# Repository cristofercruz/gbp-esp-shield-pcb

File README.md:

# Game Boy WiFi Printer - D1 Mini Shield  

<a href="https://oshpark.com/shared_projects/7WqZCkn1"></img></a>

Enthusiasts on the [Game Boy Camera Club discord server](http://bit.ly/gbccd) have been working on a Game Boy Printer emulator project based on ESP8266 D1 mini boards. Taking inspiration from other projects like the [Gameboy Link Cable Breakout PCB](https://github.com/Palmr/gb-link-cable), I created this shield board to add a link connector and pinouts for an oled screen.

Here's a render of the PCB  

# Recommended D1 mini Boards:  
**LILYGO TTGO D1 mini** (recommended) - https://www.aliexpress.com/item/4001144115302.html  
Embedded 16340 battery holder, embedded charge curcuit, and embedded power switch.

**LOLIN D1 mini Pro** - https://www.aliexpress.com/item/32724692514.html  
Embedded LiPo battery connector, embedded charge circuit. No embedded power switch.

**LOLIN D1 mini** - https://www.aliexpress.com/item/32529101036.html  
No battery connector, no charge curcit, and no power switch included.

# Assembled Printer Example  
Here's a photo of an assembled printer using a D1 mini Pro board:  

# Components  
Besides the ESP8266 board, this shield uses the following components:

* 1× 4.7kΩ resistor (*required for link detection*)
* 1x 10kΩ resistor (*required for link detection*)
* 1× 128×32 OLED display (*optional, recommended*)
* 1× 3.5mm LED (*optional*)

Placements for the components are clearly marked on the board's silkscreen. The resistors can be either through hole or surface mount type and can be placed either on the top OR bottom of the board.

# Compatible Software  
This shield breaks out appropriate pins for the Game Boy Link port that is part of the PCB itself. This hardware is suitable for both the [Arduino Game Boy Printer Emulator](https://github.com/mofosyne/arduino-gameboy-printer-emulator) as well as the [WiFi Game Boy Printer Emulator](https://github.com/HerrZatacke/wifi-gbp-emulator)

When using this with the WiFi Game Boy Printer Emulator, you can uncomment and adjust the pin on the following lines in your `config.h` file to detect a connected and powered on Game Boy to auto switch into print mode:  
```
// Sense boot mode lets you use the signal on pin GB_5V_OUT to determine printer/server mode
#define SENSE_BOOT_MODE
#define GB_5V_OUT 16
```

If you've added the optional OLED display, you can uncomment and adjust the pins on the following lines in your `config.h` file:  
```
// Uncomment if using an adafruit oled display
#define USE_OLED
// Alternative OLED Pins
#define OLED_SDA 4
#define OLED_SCL 5
```

# Usage 

When connecting a Game Boy Link cable to the shield, check the silkscreen for indicators on which side should be placed up. (The flat side of the connector should face down and the rounded side should face up, the same side as the OLED screen.)

You can get help with this project and find info on the software that runs on the ESP by joining the [Game Boy Camera Club discord server](http://bit.ly/gbccd)

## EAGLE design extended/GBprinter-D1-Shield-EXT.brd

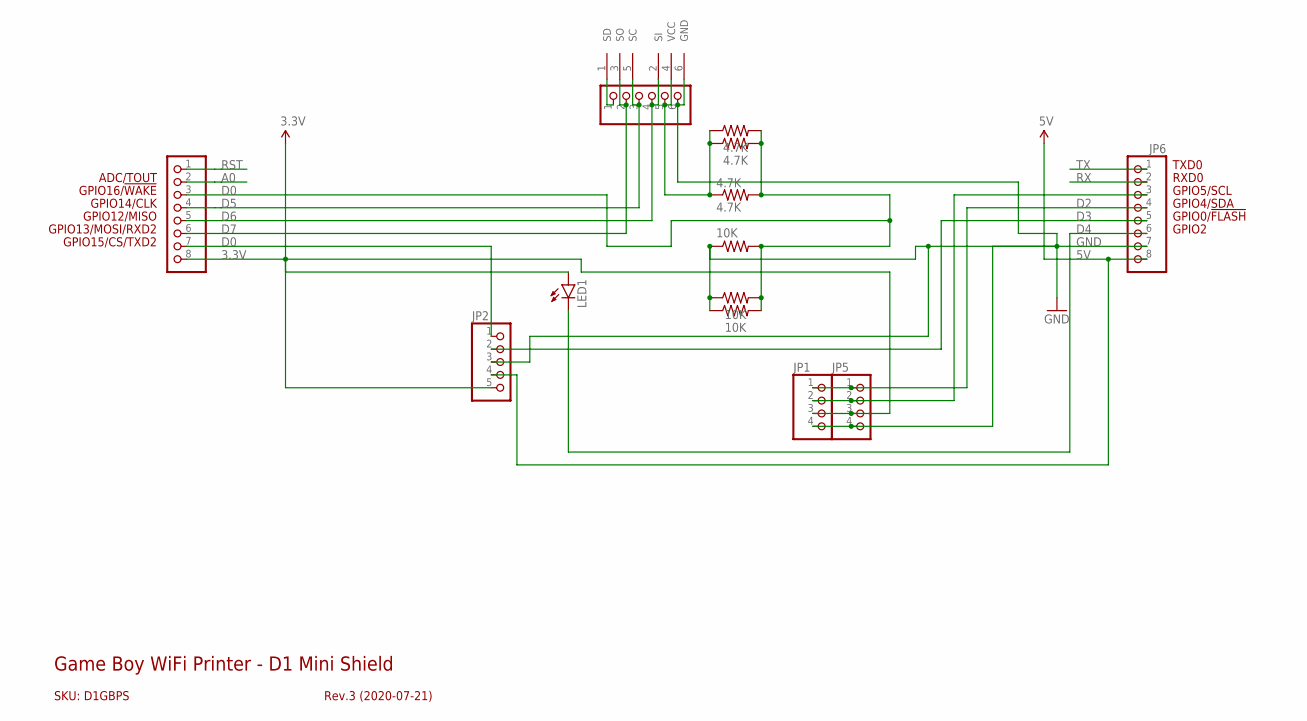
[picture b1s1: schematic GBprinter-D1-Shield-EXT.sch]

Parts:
4.7K: 4.7K; 0207/10
10K: 10K; 0207/10
JP1, JP5: PINHD-1X4/OCT; 1X04/OCT
JP2: PINHD-1X5/OCT; 1X05/OCT
JP3, JP6: PINHD-1X8/OCT; 1X08/OCT
JP4: PINHD-1X6/OCT; 1X06/OCT
LED1: LED3MM
R1, R5: 4.7K; RESC2012X65
R2, R3: 10K; RESC2012X65
U$2: GB-LINK-PADS; GB-LINK-PCB

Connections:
3.3V: JP1.3, JP2.5, JP3.8, JP5.3, LED1.A
5V: JP2.4, JP6.8
A0: JP3.2
D0: 4.7K.2, 10K.2, JP3.3, R1.2, R2.2, R3.2, R5.2
D1: JP1.2, JP5.2, JP6.3
D2: JP1.1, JP5.1, JP6.4
D3: JP2.2, JP6.5
D4: JP6.6, LED1.K (C)
D5: JP3.4, JP4.3, U$2.5 (SC)
D6: JP3.5, JP4.4, U$2.2 (SI)
D7: JP3.6, JP4.2, U$2.3 (SO)
D8: JP2.1, JP3.7
GND: 10K.1, JP1.4, JP2.3, JP4.6, JP5.4, JP6.7, R2.1, R3.1, U$2.6 (GND)
RST: JP3.1
RX: JP6.2
SD: 4.7K.1, JP4.5, R1.1, R5.1, U$2.4 (VCC)
TX: JP6.1
VCC: JP4.1, U$2.1 (SD)

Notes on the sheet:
GPIO2
GPIO0/!FLASH
GPIO12/MISO
GPIO4/SDA
GPIO5/SCL
RXD0
TXD0
GPIO13/MOSI/RXD2
GPIO14/CLK
GPIO15/CS/TXD2
GPIO16/!WAKE
SKU: D1GBPS
Game Boy WiFi Printer - D1 Mini Shield
Rev.3 (2020-07-21)
ADC/TOUT

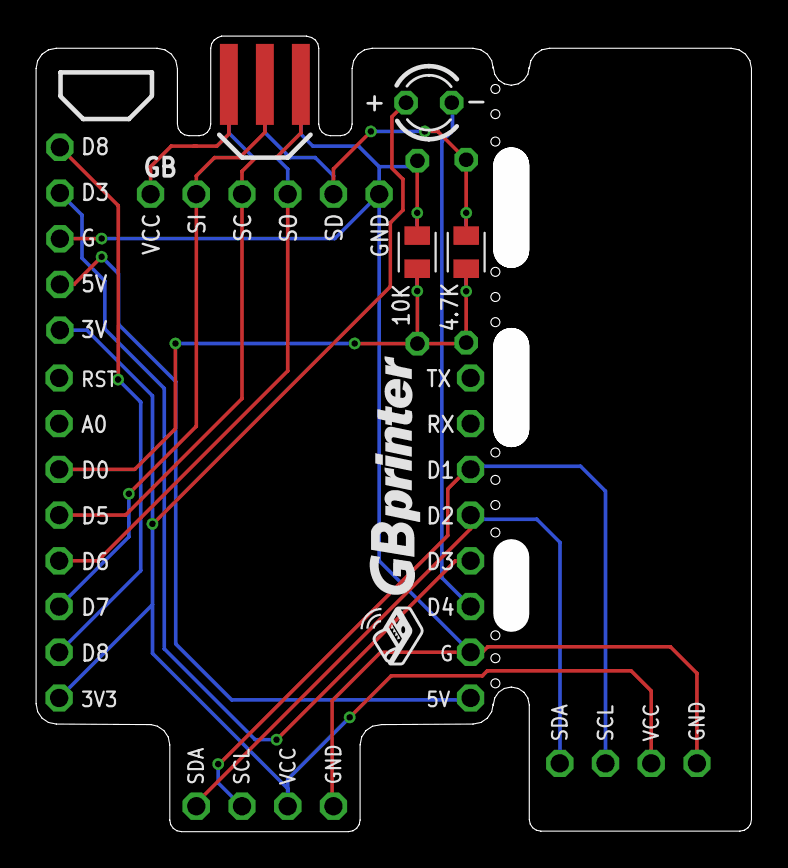
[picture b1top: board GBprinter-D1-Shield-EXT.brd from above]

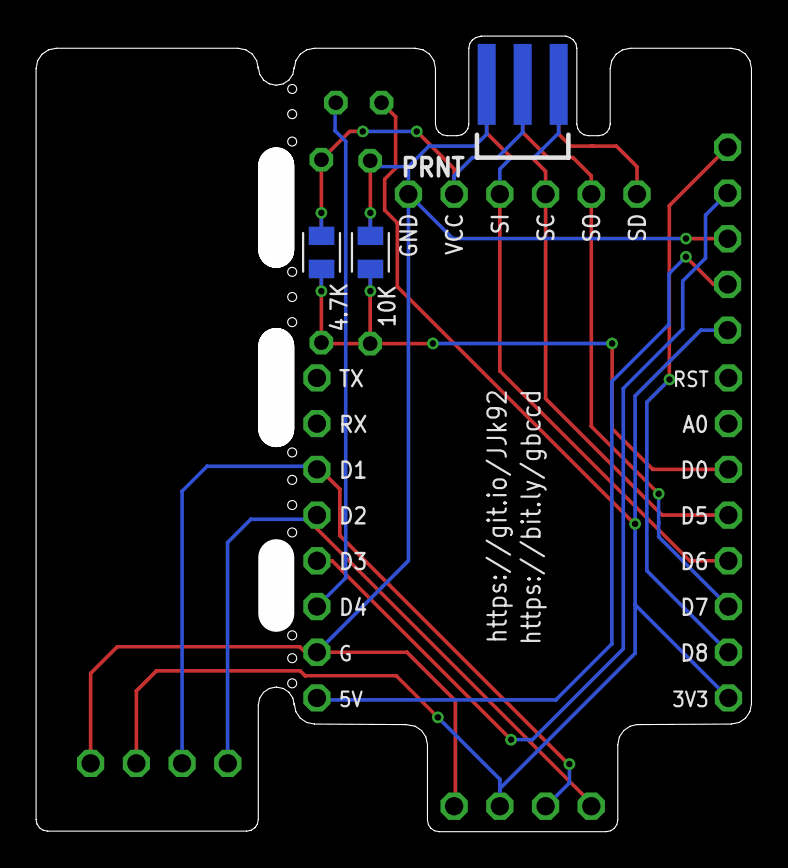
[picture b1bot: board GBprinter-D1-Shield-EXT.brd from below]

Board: 2 copper layers, 37.8 x 42.2 mm, 14 parts (4 on the bottom side), 14 nets.

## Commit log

2020-07-04 inital commit
2020-07-21 post eagle files and gerbers
2020-07-21 post eagle files, images and gerbers
2020-07-21 fix image url
2020-07-21 expand gerbers
2020-07-21 move gerbers
2021-04-24 Update README.md
    Adds useful information when connecting the PCB
2021-04-25 Adds sense boot mode to configuration
2021-08-26 Link detect switched to D0, 10K resistor added, resistors moved, cleaned up routing
2021-08-26 new assembled pic
2021-08-31 build pic

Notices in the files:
parts and their libraries:
freetronics-original: Licensing: CC v3.0 Share-Alike You are welcome to use this library for commercial purposes.
